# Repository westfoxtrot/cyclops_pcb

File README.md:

# Cyclops PCB
Custom PCB that was designed to make a more modern layout from the ISO AEK2

It employs a 66-key layout and the pcb is confirmed compatible with the following cases:

* KBD661
* KBD66
* Borsdorf

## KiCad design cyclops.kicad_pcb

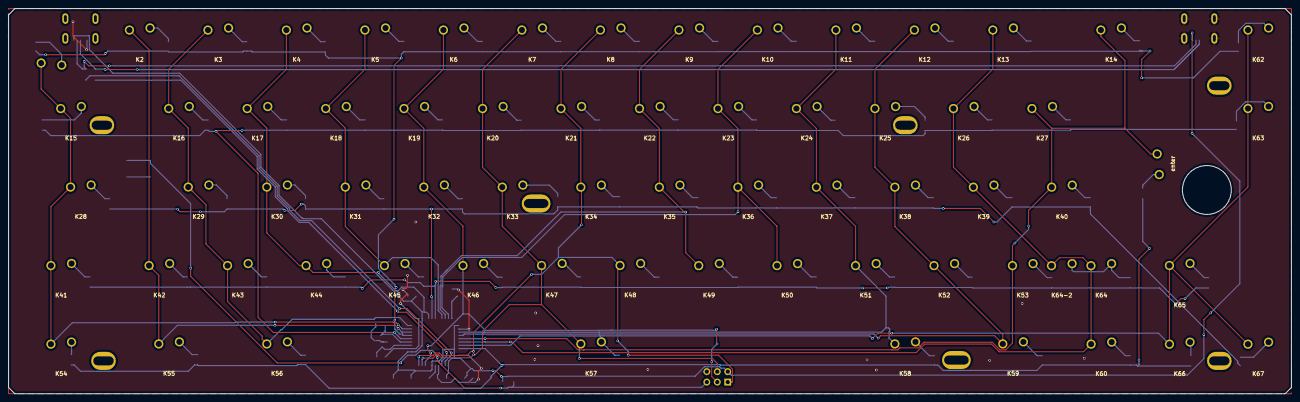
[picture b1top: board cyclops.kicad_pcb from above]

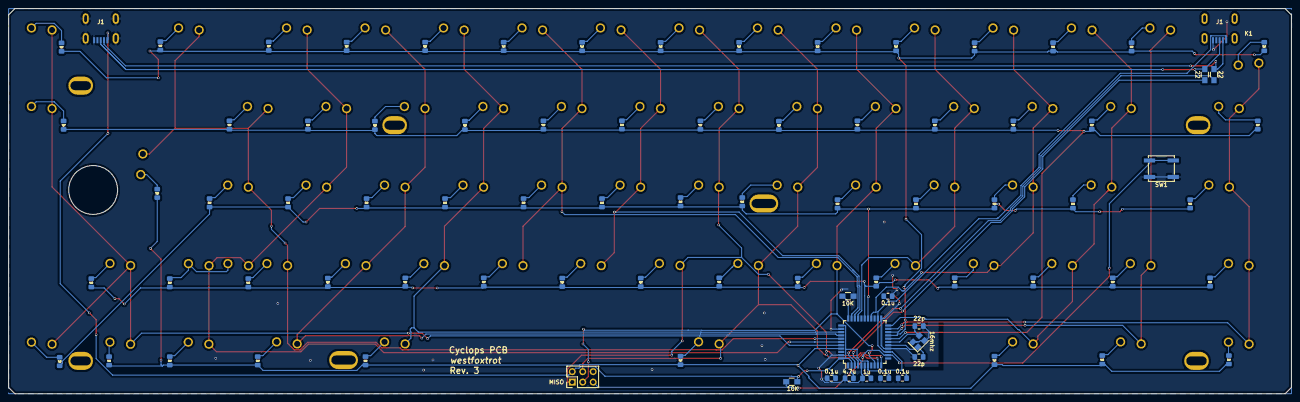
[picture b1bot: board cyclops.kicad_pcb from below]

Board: 2 copper layers, 311.4 x 93.5 mm, 160 parts (86 on the bottom side), 98 nets.

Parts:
C1, C2, C3, C4: 0.1u; C_0805_2012Metric_Pad1.15x1.40mm_HandSolder
C5: 4.7u; C_0805_2012Metric_Pad1.15x1.40mm_HandSolder
C6, C7: 22p; C_0805_2012Metric_Pad1.15x1.40mm_HandSolder
C8: 1u; C_0805_2012Metric_Pad1.15x1.40mm_HandSolder
D1, D2, D3, D4, D5, D6, D7, D8, D9, D10, D11, D12, D13, D14, D15, D16, D17, D18, D19, D20, D21, D22, D23, D24, D25, D26, D27, D28, D29, D30, D31, D32, D33, D34, D35, D36, D37, D38, D39, D40, D41, D42, D43, D44, D45, D46, D47, D48, D49, D50, D51, D52, D53, D54, D55, D56, D57, D58, D59, D60, D61, D62, D63, D64, D65, D66, D67: D; D_0805_2012Metric_Pad1.15x1.40mm_HandSolder
J1, J1#2: USB_mini_micro_B; U-M-M5DD-W-1
J2: MISO; Pin_Header_Straight_2x03_Pitch2.54mm
K1: ESC; ALPS-1.25U
K2: 1; ALPS-1U
K3, K4, K5, K6, K7, K8, K9, K10, K11, K12, K13, K16, K17, K18, K19, K20, K21, K22, K23, K24, K25, K26, K27, K29, K30, K31, K32, K33, K34, K35, K36, K37, K38, K39, K40, K42, K43, K44, K45, K46, K47, K48, K49, K50, K51, K52, K63: KEYSW; ALPS-1U
K14: backspace; ALPS-1.75U
K15: tab; ALPS-1.75U
K28: Lock; ALPS-2U
K41: Shift; ALPS-1.5U
K53, K64, K65, K66, K67: Shift; ALPS-1U
K54: Ctrl; ALPS-1.5U
K55, K59: alt; ALPS-1.25U
K56: opt; ALPS-1.5U
K57: space; ALPS-6.5U
K58: cmd; ALPS-1.5U
K60: ctrl; ALPS-1U
K61: enter; ALPS-ISO
K62: backspace; ALPS-1U
K64-2: Shift; ALPS-2U
MH1, MH1#2, MH1#3, MH1#4, MH1#5, MH1#6, MH1#7: MountingHole_2.2mm_M2_Pad
R1, R2: 22; R_0805_HandSoldering
R3, R4: 10K; R_0805_HandSoldering
SW1: SW_Push; SW_SPST_EVPBF
U1: ATMEGA32U4; TQFP-44_10x10mm_P0.8mm
X1: 16mhz; Crystal_SMD_3225-4Pin_3.2x2.5mm

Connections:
/COL0: K1.1, K15.1, K28.1, K41.1, K54.1, U1.21
/COL1: K2.1, K42.1, K55.1, U1.20
/COL2: K3.1, K16.1, K29.1, K43.1, K56.1, U1.22
/COL3: K4.1, K17.1, K30.1, K44.1, U1.26
/COL4: K5.1, K18.1, K31.1, K45.1, U1.30
/COL5: J2.3, K6.1, K19.1, K32.1, K46.1, U1.9
/COL6: J2.4, K7.1, K20.1, K33.1, K47.1, K57.1, U1.10
/COL7: J2.1, K8.1, K21.1, K34.1, K48.1, U1.11
/COL8: K9.1, K22.1, K35.1, K49.1, U1.31
/COL9: K10.1, K23.1, K36.1, K50.1, U1.32
/COL10: K11.1, K24.1, K37.1, K51.1, K58.1, U1.36
/COL11: K12.1, K25.1, K38.1, K52.1, K59.1, U1.37
/COL12: K13.1, K26.1, K39.1, K60.1, K64.1, K64-2.1, U1.39
/COL13: K14.1, K27.1, K40.1, K53.1, K61.1, U1.38
/COL14: K62.1, K63.1, K65.1, K66.1, K67.1, U1.40
/RESET: J2.5, R3.2, SW1.2, U1.13
/ROW0: D1.1, D2.1, D3.1, D4.1, D5.1, D6.1, D7.1, D8.1, D9.1, D10.1, D11.1, D12.1, D13.1, D14.1, D62.1, U1.19
/ROW1: D15.1, D16.1, D17.1, D18.1, D19.1, D20.1, D21.1, D22.1, D23.1, D24.1, D25.1, D26.1, D27.1, D63.1, U1.18
/ROW2: D28.1, D29.1, D30.1, D31.1, D32.1, D33.1, D34.1, D35.1, D36.1, D37.1, D38.1, D39.1, D40.1, D67.1, U1.27
/ROW3: D41.1, D42.1, D43.1, D44.1, D45.1, D46.1, D47.1, D48.1, D49.1, D50.1, D51.1, D52.1, D53.1, D64.1, D65.1, U1.28
/ROW4: D54.1, D55.1, D56.1, D57.1, D58.1, D59.1, D60.1, D61.1, D66.1, U1.41
GND: C1.2, C2.2, C3.2, C4.2, C5.2, C6.2, C7.2, C8.1, J1.5, J1.6, J1#2.5, J2.6, R4.2, SW1.1, U1.5, U1.15, U1.23, U1.35, U1.43, X1.2, X1.4
unnamed: C6.1, U1.17, X1.3
unnamed: C7.1, U1.16, X1.1
unnamed: C8.2, U1.6
unnamed: D1.2, K1.2
unnamed: D2.2, K2.2
unnamed: D3.2, K3.2
unnamed: D4.2, K4.2
unnamed: D5.2, K5.2
unnamed: D6.2, K6.2
unnamed: D7.2, K7.2
unnamed: D8.2, K8.2
unnamed: D9.2, K9.2
unnamed: D10.2, K10.2
unnamed: D11.2, K11.2
unnamed: D12.2, K12.2
unnamed: D13.2, K13.2
unnamed: D14.2, K14.2
unnamed: D15.2, K15.2
unnamed: D16.2, K16.2
unnamed: D17.2, K17.2
unnamed: D18.2, K18.2
unnamed: D19.2, K19.2
unnamed: D20.2, K20.2
unnamed: D21.2, K21.2
unnamed: D22.2, K22.2
unnamed: D23.2, K23.2
unnamed: D24.2, K24.2
unnamed: D25.2, K25.2
unnamed: D26.2, K26.2
unnamed: D27.2, K27.2
unnamed: D28.2, K28.2
unnamed: D29.2, K29.2
unnamed: D30.2, K30.2
unnamed: D31.2, K31.2
unnamed: D32.2, K32.2
unnamed: D33.2, K33.2
unnamed: D34.2, K34.2
unnamed: D35.2, K35.2
unnamed: D36.2, K36.2
unnamed: D37.2, K37.2
unnamed: D38.2, K38.2
unnamed: D39.2, K39.2
unnamed: D40.2, K40.2
unnamed: D41.2, K41.2
unnamed: D42.2, K42.2
unnamed: D43.2, K43.2
unnamed: D44.2, K44.2
unnamed: D45.2, K45.2
unnamed: D46.2, K46.2
unnamed: D47.2, K47.2
unnamed: D48.2, K48.2
unnamed: D49.2, K49.2
unnamed: D50.2, K50.2
unnamed: D51.2, K51.2
unnamed: D52.2, K52.2
unnamed: D53.2, K53.2
unnamed: D54.2, K54.2
unnamed: D55.2, K55.2
unnamed: D56.2, K56.2
unnamed: D57.2, K57.2
unnamed: D58.2, K58.2
unnamed: D59.2, K59.2
unnamed: D60.2, K60.2
unnamed: D61.2, K61.2
unnamed: D62.2, K62.2
unnamed: D63.2, K63.2
unnamed: D64.2, K64.2, K64-2.2
unnamed: D65.2, K65.2
unnamed: D66.2, K66.2
unnamed: D67.2, K67.2
unnamed: J1.2, J1#2.2, R2.1
unnamed: J1.3, J1#2.3, R1.1
unnamed: R1.2, U1.4
unnamed: R2.2, U1.3
unnamed: R4.1, U1.33
VCC: C1.1, C2.1, C3.1, C4.1, C5.1, J1.1, J1#2.1, J2.2, R3.1, U1.2, U1.7, U1.14, U1.24, U1.34, U1.44

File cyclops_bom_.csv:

Component,Description,Part,References,Value,Footprint,Quantity Per PCB,Datasheet
1,"Unpolarized capacitor, small symbol",C_Small,C1 C2 C3 C4,0.1u,C_0805_2012Metric_Pad1.15x1.40mm_HandSolder,4,
2,"Unpolarized capacitor, small symbol",C_Small,C8,1u,C_0805_2012Metric_Pad1.15x1.40mm_HandSolder,1,
3,"Unpolarized capacitor, small symbol",C_Small,C6 C7,22p,C_0805_2012Metric_Pad1.15x1.40mm_HandSolder,2,
4,"Unpolarized capacitor, small symbol",C_Small,C5,4.7u,C_0805_2012Metric_Pad1.15x1.40mm_HandSolder,1,
5,Diode,D,D1 D2 D3 D4 D5 D6 D7 D8 D9 D10 D11 D12 D13 D14 D15 D16 D17 D18 D19 D20 D21 D22 D23 D24 D25 D26 D27 D28 D29 D30 D31 D32 D33 D34 D35 D36 D37 D38 D39 D40 D41 D42 D43 D44 D45 D46 D47 D48 D49 D50 D51 D52 D53 D54 D55 D56 D57 D58 D59 D60 D61 D62 D63 D64 D65 D66 D67,D,D_0805_2012Metric_Pad1.15x1.40mm_HandSolder,67,
7,,USB_mini_micro_B-keyboard_parts,J1,USB_mini_micro_B,U-M-M5DD-W-1,1,
25,"Resistor, small symbol",R_Small,R3 R4,10K,R_0805_HandSoldering,2,
26,Resistor,R,R1 R2,22,R_0805_HandSoldering,2,
27,,SW_Push-switches,SW1,SW_Push,SW_SPST_EVPBF,1,
28,,ATMEGA32U4-keyboard_parts,U1,ATMEGA32U4,TQFP-44_10x10mm_P0.8mm,1,
29,,Crystal_GND24_Small-Device,X1,Crystal_3225,Crystal_SMD_3225-4Pin_3.2x2.5mm,1,

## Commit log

2017-12-15 schematic done
2017-12-20 PCB layout complete
2018-01-03 pcb complete
2018-01-03 revised pcb
2018-01-03 pcb minor fixes
2018-01-03 Move mcu components out temporarily
2018-01-03 Correct the crystal
2018-01-03 Move MCU back into place
2018-01-03 Move MCU up
2018-01-03 Finish MCU breakout
2018-01-03 Clean some routing
2018-11-28 Revised design entirely
    changed to 66-key
2018-12-28 Updated to Rev. 3
    corrected some issues with footprints
    adjusted some traces to be less close to easily damaged parts
    added silkscreen details for the board
    adjusted iso footprint
    changed some footrprints to updated ones
    updated gerbers
2018-12-28 minor adjustment of D1
2018-12-29 Updated layout of decoupling caps
    generated new gerbers
2020-08-09 added bom
